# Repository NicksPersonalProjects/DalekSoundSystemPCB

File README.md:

# DalekSoundSystemPCB
Versions of a custom PCB designed in KiCad for the RC Dalek that I've helped build

The broad purpose of this board is to consolidate some pre-existing systems and get practice making PCBs and using STM32 Chips as the MCU.

## Board Functions
More specifically, this board is designed to take 4 different PWM signals generated by an RC reciever as inputs, each is used to control separate functions:  
  - **PWM Input 1** is used to control the <ins>DWTheme Function</ins>, designed to play the Doctor Who Theme from the main speakers of the Dalek on loop as long as the toggle is on. It sends the audio through the **Audio Out** Output of the board and the audio is produced by the DF Mini Player.  
  - **PWM Input 2** is used to control the <ins>Main Lights Function</ins>, which turns on or off the external lights on the Dalek with a toggle swtich. Said lights are powered by the 12V battery on board the Dalek which are inputted through the **12V In** in put and the lights are connected to the **Lights Out** Output.  
  - **PWM Input 3** is used to control the <ins>Exterminate Function</ins>, which simply makes the Dalek exclaim Exterminate via the same method as the <ins>DWTheme Function</ins>.  
  - **PWM Input 4** is used to control the <ins>Blaster Function</ins>, which plays the corresponding Blaster sound via the same method as the <ins>DWTheme Function</ins> and controls RGB LEDs in a specific pattern to simulate a laser blaster. The Blaster LEDs are controled through the **LED Out** Output  

Additionally this board features a volume knob to independantly control the volume of any sounds produced by this board  

## Quality of Life Features
This Board also features some QOL features meant for helping bench test and future proofing such as:
- Breaking out every unused pin to its own header
- Organizing other pins used for different communication standards such as SPI or I2C
- Two additional PWM Inputs for potential future functions
- A USB Port so the board can be powered at a test bench
- An LED to indicate the board has power
- Header pins connected to UART4 which controls the DF Mini Player for monitoring
- An LED connected to the DF Mini Player to indicate when it is playing sound
- A push button used to facilitate testing

## Other Important Notes
This Board is designed to be powered off of 5V power which is stepped down to 3.3V for the MCU. The board gets power from the USB port while bench testing and from the 5V pin on "PWM Input 1" when implimented in the Dalek  

All Parts used in fabrication have their datasheets linked in the project schematic aside from some basic parts that were already on hand as well as the MCU which is a STM32F100RDT6B chip  

V1 of this board is currently outdated and poorly designed  
V2 is the current version  of the board used in the actual robot (minus some minor improvements made since)

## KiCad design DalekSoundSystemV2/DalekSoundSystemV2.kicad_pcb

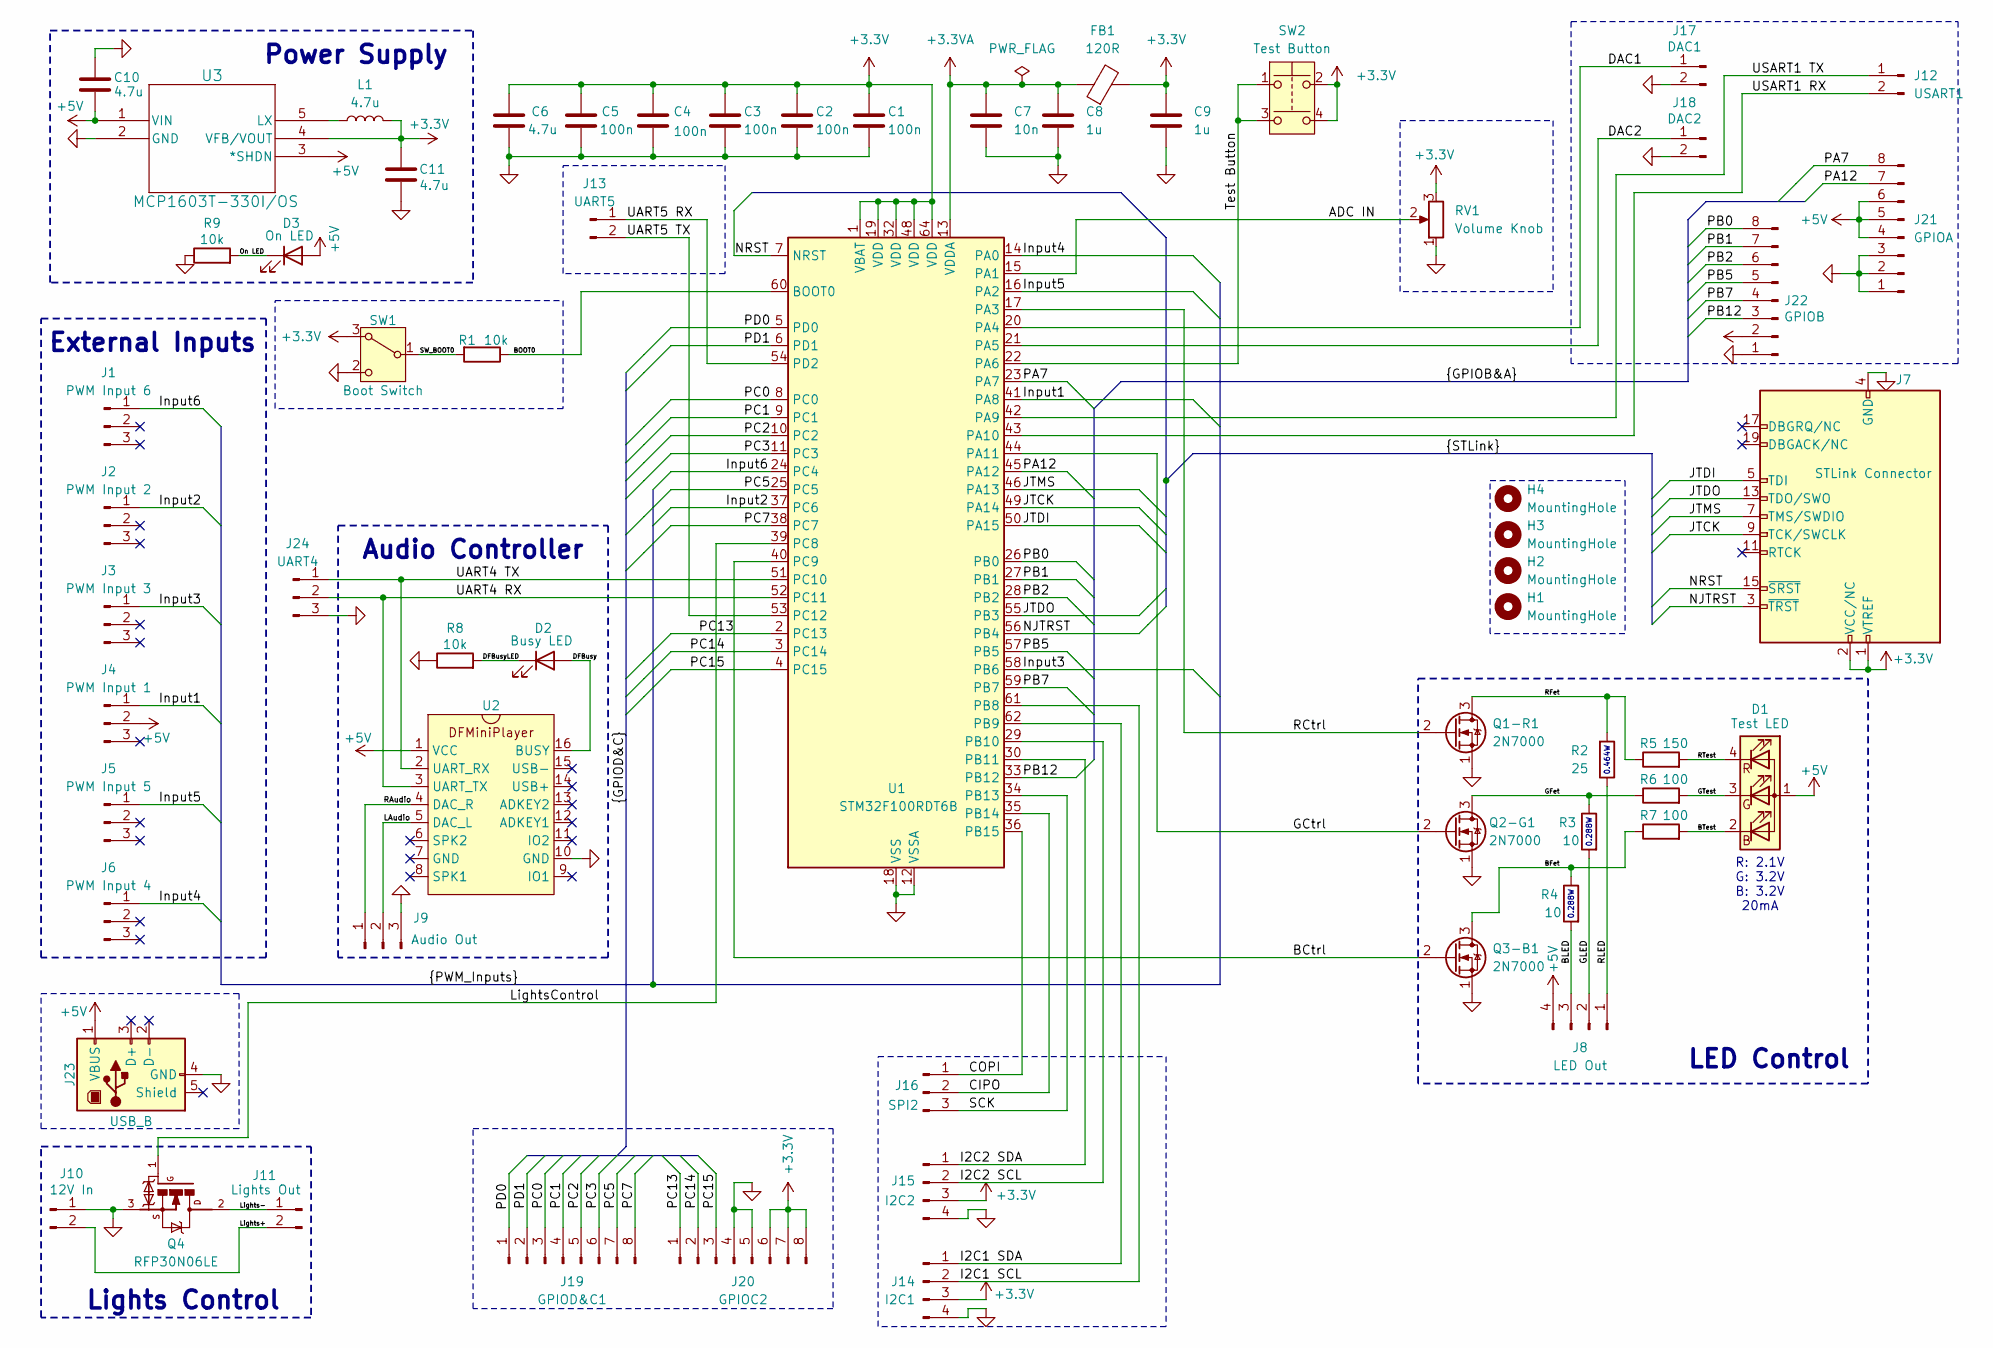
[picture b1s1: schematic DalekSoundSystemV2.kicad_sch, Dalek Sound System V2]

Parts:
C1, C2, C3, C4, C5: 100n; C_0402_1005Metric_Pad0.74x0.62mm_HandSolder
C6, C10, C11: 4.7u; C_0402_1005Metric_Pad0.74x0.62mm_HandSolder
C7: 10n; C_0402_1005Metric_Pad0.74x0.62mm_HandSolder
C8, C9: 1u; C_0402_1005Metric_Pad0.74x0.62mm_HandSolder
D1: Test LED; LED_BL-FL7680RGB-wEdge
D2: Busy LED; LED_D5.0mm
D3: On LED; LED_D5.0mm
FB1: 120R; L_0402_1005Metric_Pad0.77x0.64mm_HandSolder
H1, H2, H3, H4: MountingHole; MountingHole_3.5mm
J1: PWM Input 6; PinHeader_1x03_P2.54mm_Vertical
J2: PWM Input 2; PinHeader_1x03_P2.54mm_Vertical
J3: PWM Input 3; PinHeader_1x03_P2.54mm_Vertical
J4: PWM Input 1; PinHeader_1x03_P2.54mm_Vertical
J5: PWM Input 5; PinHeader_1x03_P2.54mm_Vertical
J6: PWM Input 4; PinHeader_1x03_P2.54mm_Vertical
J7: STLink Connector; PinHeader_2x10_P2.54mm_Vertical
J8: LED Out; CONN_SD-43650-010_04_MOLEX4PINSOCKET
J9: Audio Out; CONN_SD-43650-010_03_MOLEX3PINSOCKET
J10: 12V In; CONN_SD-43650-010_02_MOLEX2PINSOCKET
J11: Lights Out; CONN_SD-43650-010_02_MOLEX2PINSOCKET
J12: USART1; PinHeader_1x02_P2.54mm_Vertical
J13: UART5; PinHeader_1x02_P2.54mm_Vertical
J14: I2C1; PinHeader_1x04_P2.54mm_Vertical
J15: I2C2; PinHeader_1x04_P2.54mm_Vertical
J16: SPI2; PinHeader_1x03_P2.54mm_Vertical
J17: DAC1; PinHeader_2x01_P2.54mm_Vertical
J18: DAC2; PinHeader_2x01_P2.54mm_Vertical
J19: GPIOD&C1; PinHeader_1x08_P2.54mm_Vertical
J20: GPIOC2; PinHeader_1x08_P2.54mm_Vertical
J21: GPIOA; PinHeader_1x08_P2.54mm_Vertical
J22: GPIOB; PinHeader_1x08_P2.54mm_Vertical
J23: USB_B; USB_B_OST_USB-B1HSxx_Horizontal
J24: UART4; PinHeader_1x03_P2.54mm_Vertical
L1: 4.7u; L_0402_1005Metric_Pad0.77x0.64mm_HandSolder
Q1-R1, Q2-G1, Q3-B1: 2N7000; TO-92_Inline
Q4: RFP30N06LE; TRANS_RFP30N06LE
R1, R8, R9: 10k; R_0603_1608Metric_Pad0.98x0.95mm_HandSolder
R2: 25; R_0603_1608Metric_Pad0.98x0.95mm_HandSolder
R3, R4: 10; R_0603_1608Metric_Pad0.98x0.95mm_HandSolder
R5: 150; R_0603_1608Metric_Pad0.98x0.95mm_HandSolder
R6, R7: 100; R_0603_1608Metric_Pad0.98x0.95mm_HandSolder
RV1: Volume Knob; Potentiometer_Alpha_RD901F-40-00D_Single_Vertical
SW1: Boot Switch; SW_Slide-03_Wuerth-WS-SLTV_10x2.5x6.4_P2.54mm
SW2: Test Button; Push Button
U1: STM32F100RDT6B; LQFP-64_10x10mm_P0.5mm
U2: DFMiniPlayer
U3: MCP1603T-330I/OS; TSOT5_MC_MCH

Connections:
+3.3V: C1.1, C2.1, C3.1, C4.1, C5.1, C6.1, C9.1, C11.2, FB1.2, J7.1 (VTREF), J7.2 (VCC/NC), J14.3, J15.3, J20.6, J20.7, J20.8, L1.2, RV1.3, SW1.3 (A), SW2.2, SW2.4, U1.1 (VBAT), U1.19 (VDD), U1.32 (VDD), U1.48 (VDD), U1.64 (VDD), U3.4 (VFB/VOUT)
+3.3VA: C7.1, C8.1, FB1.1, U1.13 (VDDA)
+5V: C10.2, D1.1 (A), D3.2 (A), J4.2, J8.4, J21.4, J21.5, J21.6, J22.2, J23.1 (VBUS), U2.1 (VCC), U3.1 (VIN), U3.3 (*SHDN)
/ADC IN: RV1.2, U1.15 (PA1)
/BCtrl: Q3-B1.2 (G), U1.40 (PC9)
/BFet: Q3-B1.3 (D), R4.1, R7.1
/BLED: J8.3, R4.2
/BOOT0: R1.1, U1.60 (BOOT0)
/BTest: D1.2 (BK), R7.2
/CIPO: J16.2, U1.35 (PB14)
/COPI: J16.1, U1.36 (PB15)
/DAC1: J17.1, U1.20 (PA4)
/DAC2: J18.1, U1.21 (PA5)
/DFBusy: D2.2 (A), U2.16 (BUSY)
/DFBusyLED: D2.1 (K), R8.2
/GCtrl: Q2-G1.2 (G), U1.44 (PA11)
/GFet: Q2-G1.3 (D), R3.1, R6.1
/GLED: J8.2, R3.2
/GTest: D1.3 (GK), R6.2
/I2C1 SCL: J14.2, U1.61 (PB8)
/I2C1 SDA: J14.1, U1.62 (PB9)
/I2C2 SCL: J15.2, U1.29 (PB10)
/I2C2 SDA: J15.1, U1.30 (PB11)
/Input1: J4.1, U1.41 (PA8)
/Input2: J2.1, U1.37 (PC6)
/Input3: J3.1, U1.58 (PB6)
/Input4: J6.1, U1.14 (PA0)
/Input5: J5.1, U1.16 (PA2)
/Input6: J1.1, U1.24 (PC4)
/JTCK: J7.9 (TCK/SWCLK), U1.49 (PA14)
/JTDI: J7.5 (TDI), U1.50 (PA15)
/JTDO: J7.13 (TDO/SWO), U1.55 (PB3)
/JTMS: J7.7 (TMS/SWDIO), U1.46 (PA13)
/LAudio: J9.2, U2.5 (DAC_L)
/Lights+: J10.2, J11.2
/Lights-: J11.1, Q4.2
/LightsControl: Q4.1, U1.39 (PC8)
/NJTRST: J7.3 (~TRST), U1.56 (PB4)
/NRST: J7.15 (~SRST), U1.7 (NRST)
/On LED: D3.1 (K), R9.2
/PA7: J21.8, U1.23 (PA7)
/PA12: J21.7, U1.45 (PA12)
/PB0: J22.8, U1.26 (PB0)
/PB1: J22.7, U1.27 (PB1)
/PB2: J22.6, U1.28 (PB2)
/PB5: J22.5, U1.57 (PB5)
/PB7: J22.4, U1.59 (PB7)
/PB12: J22.3, U1.33 (PB12)
/PC0: J19.3, U1.8 (PC0)
/PC1: J19.4, U1.9 (PC1)
/PC2: J19.5, U1.10 (PC2)
/PC3: J19.6, U1.11 (PC3)
/PC5: J19.7, U1.25 (PC5)
/PC7: J19.8, U1.38 (PC7)
/PC13: J20.1, U1.2 (PC13)
/PC14: J20.2, U1.3 (PC14)
/PC15: J20.3, U1.4 (PC15)
/PD0: J19.1, U1.5 (PD0)
/PD1: J19.2, U1.6 (PD1)
/RAudio: J9.1, U2.4 (DAC_R)
/RCtrl: Q1-R1.2 (G), U1.17 (PA3)
/RFet: Q1-R1.3 (D), R2.2, R5.1
/RLED: J8.1, R2.1
/RTest: D1.4 (RK), R5.2
/SCK: J16.3, U1.34 (PB13)
/SW_BOOT0: R1.2, SW1.1 (B)
/Test Button: SW2.1, SW2.3, U1.22 (PA6)
/UART4 RX: J24.2, U1.52 (PC11), U2.3 (UART_TX)
/UART4 TX: J24.1, U1.51 (PC10), U2.2 (UART_RX)
/UART5 RX: J13.1, U1.54 (PD2)
/UART5 TX: J13.2, U1.53 (PC12)
/USART1 RX: J12.2, U1.43 (PA10)
/USART1 TX: J12.1, U1.42 (PA9)
GND: C1.2, C2.2, C3.2, C4.2, C5.2, C6.2, C7.2, C8.2, C9.2, C10.1, C11.1, J7.4 (GND), J7.6 (GND), J7.8 (GND), J7.10 (GND), J7.12 (GND), J7.14 (GND), J7.16 (GND), J7.18 (GND), J7.20 (GND), J9.3, J10.1, J14.4, J15.4, J17.2, J18.2, J20.4, J20.5, J21.1, J21.2, J21.3, J22.1, J23.4 (GND), J24.3, Q1-R1.1 (S), Q2-G1.1 (S), Q3-B1.1 (S), Q4.3, R8.1, R9.1, RV1.1, SW1.2 (C), U1.12 (VSSA), U1.18 (VSS), U1.31 (VSS), U1.47 (VSS), U1.63 (VSS), U2.10 (GND), U3.2 (GND)
unnamed: L1.1, U3.5 (LX)

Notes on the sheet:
R: 2.1V G: 3.2V B: 3.2V 20mA
LED Control
0.464W
Audio Controller
Lights Control
External Inputs
0.288W
Power Supply

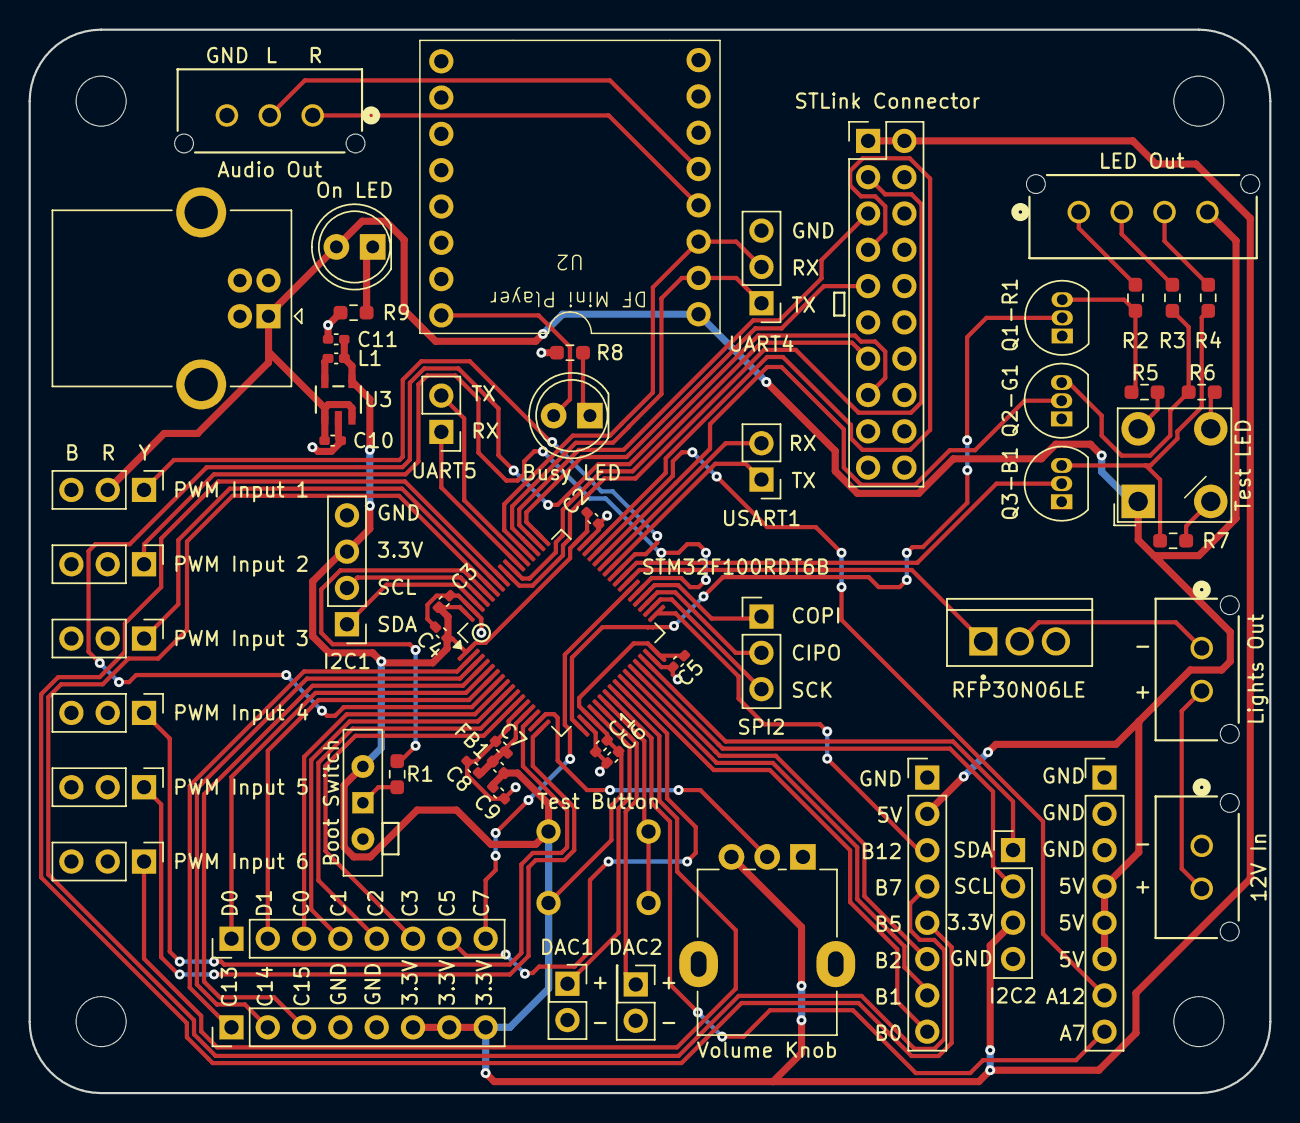
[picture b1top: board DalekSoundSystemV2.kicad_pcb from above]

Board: 2 copper layers, 86.8 x 74.4 mm, 63 parts (0 on the bottom side), 75 nets.

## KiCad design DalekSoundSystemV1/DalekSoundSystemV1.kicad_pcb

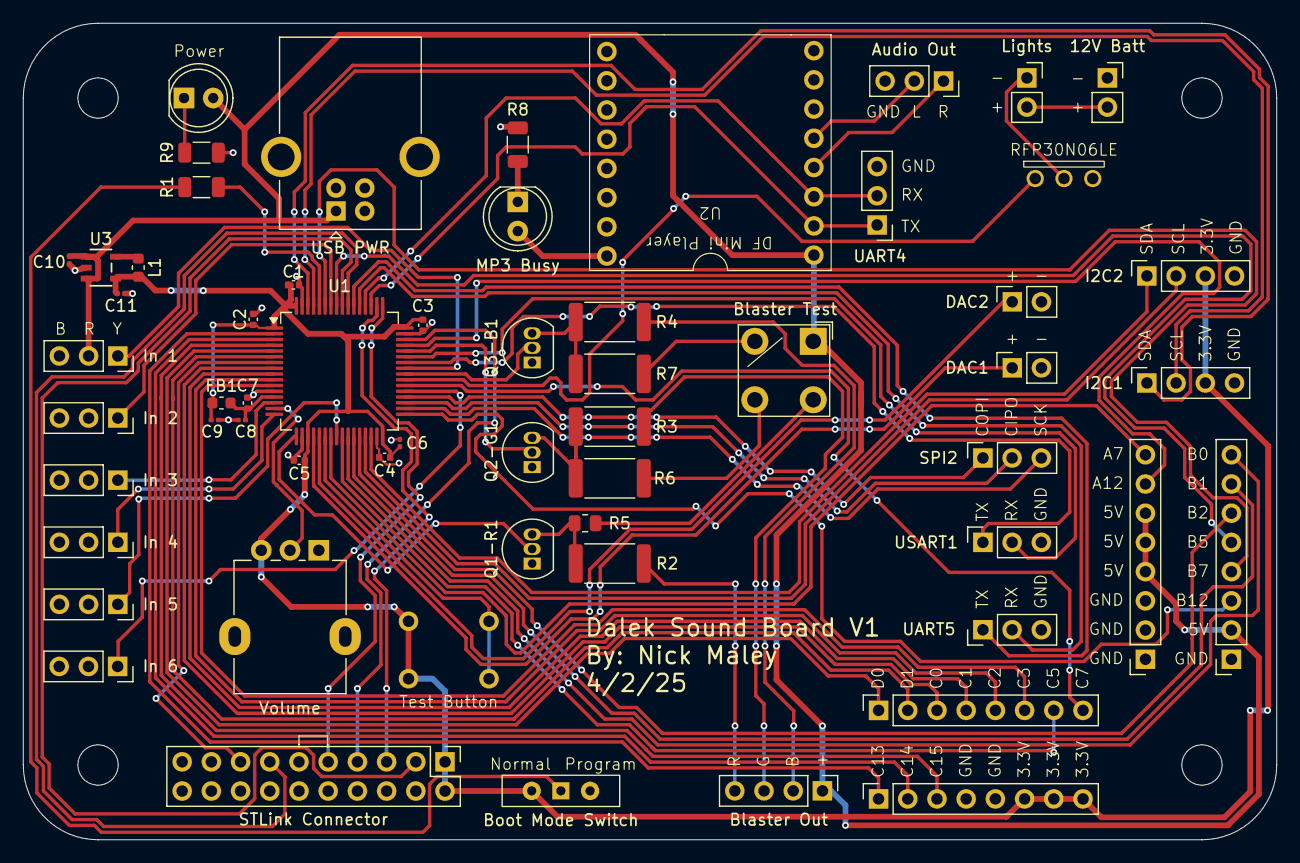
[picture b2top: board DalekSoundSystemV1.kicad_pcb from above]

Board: 2 copper layers, 109.0 x 71.0 mm, 63 parts (0 on the bottom side), 75 nets.

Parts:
12V Batt: 12V In; PinSocket_1x02_P2.54mm_Vertical
Audio Out: Audio Out; PinSocket_1x03_P2.54mm_Vertical
Blaster Out: LED Out; PinHeader_1x04_P2.54mm_Vertical
Blaster Test: Test LED; LED_BL-FL7680RGB
Boot Mode Switch: Boot Switch; SW_Slide-03_Wuerth-WS-SLTV_10x2.5x6.4_P2.54mm
C1, C2, C3, C4, C5: 100n; C_0402_1005Metric
C6, C10, C11: 4.7u; C_0201_0603Metric
C7: 10n; C_0402_1005Metric
C8, C9: 1u; C_0201_0603Metric
D3: On LED; LED_D5.0mm
DAC1: DAC1; PinSocket_1x02_P2.54mm_Vertical
DAC2: DAC2; PinSocket_1x02_P2.54mm_Vertical
FB1: 120R; L_0603_1608Metric
H1, H2, H3, H4: MountingHole; MountingHole_3.5mm
I2C1: I2C1; PinSocket_1x04_P2.54mm_Vertical
I2C2: I2C2; PinSocket_1x04_P2.54mm_Vertical
In 1: PWM Input 4; PinSocket_1x03_P2.54mm_Vertical
In 2: PWM Input 3; PinSocket_1x03_P2.54mm_Vertical
In 3: PWM Input 6; PinSocket_1x03_P2.54mm_Vertical
In 4: PWM Input 5; PinSocket_1x03_P2.54mm_Vertical
In 5: PWM Input 1; PinSocket_1x03_P2.54mm_Vertical
In 6: PWM Input 2; PinSocket_1x03_P2.54mm_Vertical
J19: GPIOD&C1; PinSocket_1x08_P2.54mm_Vertical
J20: GPIOC2; PinSocket_1x08_P2.54mm_Vertical
J21: GPIOA; PinSocket_1x08_P2.54mm_Vertical
J22: GPIOB; PinSocket_1x08_P2.54mm_Vertical
L1: 4.7u; L_0603_1608Metric
Lights: Lights Out; PinSocket_1x02_P2.54mm_Vertical
MP3 Busy: Busy LED; LED_D5.0mm
Q1-R1, Q2-G1, Q3-B1: 2N7000; TO-92_Inline
R1, R8, R9: 10k; R_1206_3216Metric
R2: 12; R_2512_6332Metric
R3, R4: 10; R_2512_6332Metric
R5: 150; R_0805_2012Metric
R6, R7: 100; R_2512_6332Metric
RFP30N06LE: 30N06L; L7805 VReg
SPI2: SPI2; PinSocket_1x03_P2.54mm_Vertical
STLink Connector: STLink Connector; PinHeader_2x10_P2.54mm_Vertical
Test Button: Test Button; Push Button
U1: STM32F100RDT6B; LQFP-64_10x10mm_P0.5mm
U2: DFMiniPlayer
U3: MCP1603T-330I/OS; TSOT5_MC_MCH
UART4: UART4 Test; PinHeader_1x03_P2.54mm_Vertical
UART5: UART5; PinHeader_1x03_P2.54mm_Vertical
USART1: USART1; PinSocket_1x03_P2.54mm_Vertical
USB PWR: USB_B; USB_B_OST_USB-B1HSxx_Horizontal
Volume: Volume Knob; Potentiometer_Alpha_RD901F-40-00D_Single_Vertical

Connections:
+3.3V: Boot Mode Switch.3 (A), C1.1, C2.1, C3.1, C4.1, C5.1, C6.1, C9.1, C11.2, FB1.2, I2C1.3, I2C2.3, J20.6, J20.7, J20.8, L1.2, STLink Connector.1 (VTREF), STLink Connector.2 (VCC/NC), Test Button.2, Test Button.4, U1.1 (VBAT), U1.19 (VDD), U1.32 (VDD), U1.48 (VDD), U1.64 (VDD), U3.4 (VFB/VOUT), Volume.3
+3.3VA: C7.1, C8.1, FB1.1, U1.13 (VDDA)
+5V: Blaster Out.1, Blaster Test.1 (A), C10.2, D3.2 (A), In 1.2, J21.4, J21.5, J21.6, J22.2, U2.1 (VCC), U3.1 (VIN), U3.3 (*SHDN), USB PWR.1 (VBUS)
/ADC IN: U1.15 (PA1), Volume.2
/BCtrl: Q3-B1.2 (G), U1.40 (PC9)
/BFet: Q3-B1.3 (D), R4.1, R7.1
/BLED: Blaster Out.2, R4.2
/BOOT0: R1.1, U1.60 (BOOT0)
/BTest: Blaster Test.2 (BK), R7.2
/CIPO: SPI2.2, U1.35 (PB14)
/COPI: SPI2.1, U1.36 (PB15)
/DAC1: DAC1.1, U1.20 (PA4)
/DAC2: DAC2.1, U1.21 (PA5)
/DFBusy: MP3 Busy.2 (A), U2.16 (BUSY)
/DFBusyLED: MP3 Busy.1 (K), R8.2
/GCtrl: Q2-G1.2 (G), U1.44 (PA11)
/GFet: Q2-G1.3 (D), R3.1, R6.1
/GLED: Blaster Out.3, R3.2
/GTest: Blaster Test.3 (GK), R6.2
/I2C1 SCL: I2C1.2, U1.61 (PB8)
/I2C1 SDA: I2C1.1, U1.62 (PB9)
/I2C2 SCL: I2C2.2, U1.29 (PB10)
/I2C2 SDA: I2C2.1, U1.30 (PB11)
/Input1: In 5.1, U1.24 (PC4)
/Input2: In 6.1, U1.37 (PC6)
/Input3: In 2.1, U1.58 (PB6)
/Input4: In 1.1, U1.41 (PA8)
/Input5: In 4.1, U1.16 (PA2)
/Input6: In 3.1, U1.14 (PA0)
/JTCK: STLink Connector.9 (TCK/SWCLK), U1.49 (PA14)
/JTDI: STLink Connector.5 (TDI), U1.50 (PA15)
/JTDO: STLink Connector.13 (TDO/SWO), U1.55 (PB3)
/JTMS: STLink Connector.7 (TMS/SWDIO), U1.46 (PA13)
/LAudio: Audio Out.2, U2.5 (DAC_L)
/Lights+: 12V Batt.2, Lights.2
/Lights-: Lights.1, RFP30N06LE.2 (D)
/LightsControl: RFP30N06LE.1 (G), U1.39 (PC8)
/NJTRST: STLink Connector.3 (~TRST), U1.56 (PB4)
/NRST: STLink Connector.15 (~SRST), U1.7 (NRST)
/On LED: D3.1 (K), R9.2
/PA7: J21.8, U1.23 (PA7)
/PA12: J21.7, U1.45 (PA12)
/PB0: J22.8, U1.26 (PB0)
/PB1: J22.7, U1.27 (PB1)
/PB2: J22.6, U1.28 (PB2)
/PB5: J22.5, U1.57 (PB5)
/PB7: J22.4, U1.59 (PB7)
/PB12: J22.3, U1.33 (PB12)
/PC0: J19.3, U1.8 (PC0)
/PC1: J19.4, U1.9 (PC1)
/PC2: J19.5, U1.10 (PC2)
/PC3: J19.6, U1.11 (PC3)
/PC5: J19.7, U1.25 (PC5)
/PC7: J19.8, U1.38 (PC7)
/PC13: J20.1, U1.2 (PC13)
/PC14: J20.2, U1.3 (PC14)
/PC15: J20.3, U1.4 (PC15)
/PD0: J19.1, U1.5 (PD0)
/PD1: J19.2, U1.6 (PD1)
/RAudio: Audio Out.1, U2.4 (DAC_R)
/RCtrl: Q1-R1.2 (G), U1.17 (PA3)
/RFet: Q1-R1.3 (D), R2.2, R5.1
/RLED: Blaster Out.4, R2.1
/RTest: Blaster Test.4 (RK), R5.2
/SCK: SPI2.3, U1.34 (PB13)
/SW_BOOT0: Boot Mode Switch.1 (B), R1.2
/Test Button: Test Button.1, Test Button.3, U1.22 (PA6)
/UART4 RX: U1.52 (PC11), U2.3 (UART_TX), UART4.2
/UART4 TX: U1.51 (PC10), U2.2 (UART_RX), UART4.1
/UART5 RX: U1.54 (PD2), UART5.1
/UART5 TX: U1.53 (PC12), UART5.2
/USART1 RX: U1.43 (PA10), USART1.2
/USART1 TX: U1.42 (PA9), USART1.1
GND: 12V Batt.1, Audio Out.3, Boot Mode Switch.2 (C), C1.2, C2.2, C3.2, C4.2, C5.2, C6.2, C7.2, C8.2, C9.2, C10.1, C11.1, DAC1.2, DAC2.2, I2C1.4, I2C2.4, J20.4, J20.5, J21.1, J21.2, J21.3, J22.1, Q1-R1.1 (S), Q2-G1.1 (S), Q3-B1.1 (S), R8.1, R9.1, RFP30N06LE.3 (S), STLink Connector.4 (GND), STLink Connector.6 (GND), STLink Connector.8 (GND), STLink Connector.10 (GND), STLink Connector.12 (GND), STLink Connector.14 (GND), STLink Connector.16 (GND), STLink Connector.18 (GND), STLink Connector.20 (GND), U1.12 (VSSA), U1.18 (VSS), U1.31 (VSS), U1.47 (VSS), U1.63 (VSS), U2.10 (GND), U3.2 (GND), UART4.3, UART5.3, USART1.3, USB PWR.4 (GND), Volume.1
unnamed: L1.1, U3.5 (LX)
